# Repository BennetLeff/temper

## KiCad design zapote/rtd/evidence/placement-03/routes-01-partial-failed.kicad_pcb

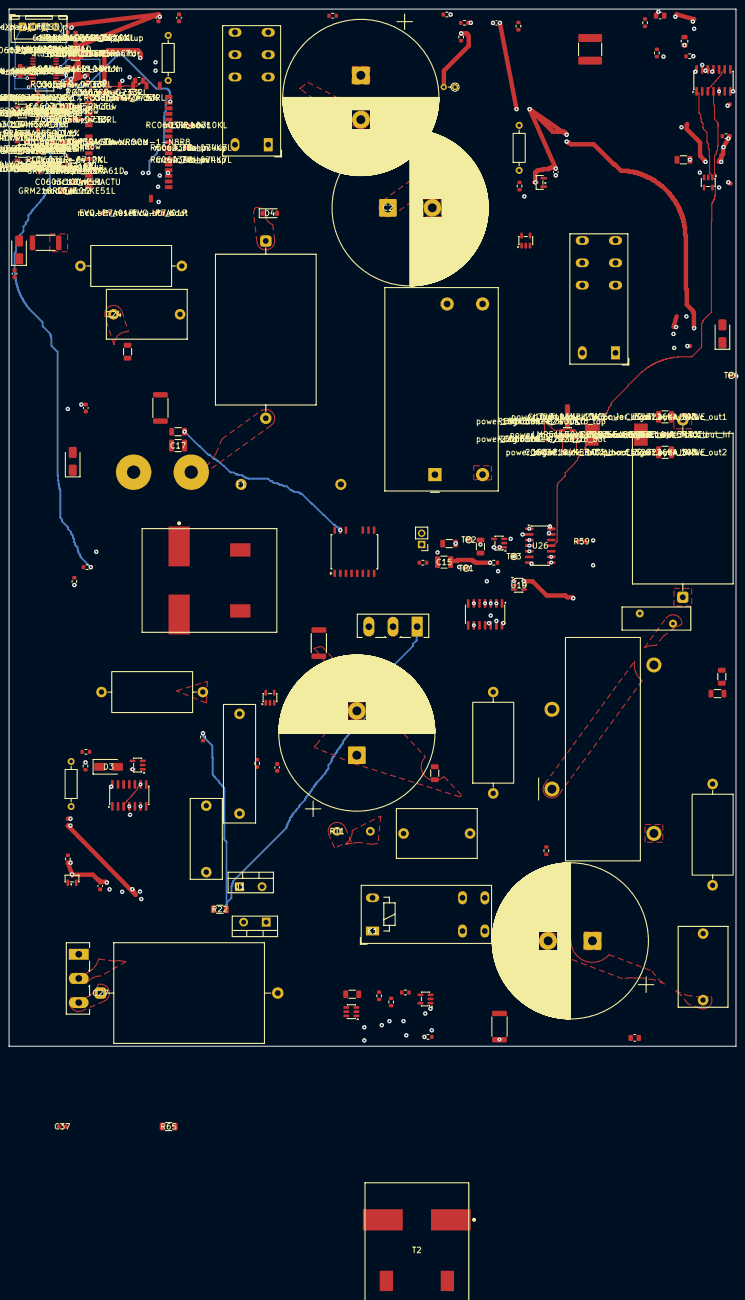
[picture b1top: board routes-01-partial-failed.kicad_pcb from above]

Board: 6 copper layers, 164.0 x 234.0 mm, 168 parts (0 on the bottom side), 110 nets.

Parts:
C1: ?; C_Rect_L18.0mm_W7.0mm_P15.00mm_FKS3_FKP3
C2, C3, C4, C5: ?; CP_Radial_D35.0mm_P10.00mm_SnapIn
C6: ?; C_Rect_L26.5mm_W7.0mm_P22.50mm_MKS4
C7, C8, C24: ?; C_Rect_L18.0mm_W11.0mm_P15.00mm_FKS3_FKP3
C9: CL32B106KBJZW6E; C_1210_3225Metric
C10, C13, C29, C30, C31, C32, C33, C34, C35, C39: C0603C104K5RACTU; C_0603_1608Metric
C11, C12: CL32B226KAJNNWE; C_1210_3225Metric
C14: ?; C_2220_5750Metric
C15, C17: ?; C_1210_3225Metric
C16, C18, C19, C20, C21, C22, C23, C28, C36, C37, C38: ?; C_0603_1608Metric
C25, C26, C27: ?; C_Axial_L34.0mm_D22.5mm_P40.00mm_Horizontal
C40: GRM21BR71A106KE51L; C_0805_2012Metric
C41: GRM188R71A105KA61D; C_0603_1608Metric
D1, D2, D3: ?; D_SMA
D4: ?; D_SOD-123
F1: ?; Fuse_Holder_5x20mm
J1: B4B-XH-A(LF)(SN); JST_XH_B4B-XH-A_1x04_P2.50mm_Vertical
J2: ?; PinHeader_1x02_P2.54mm_Vertical
K1: ?; Relay_SPST_Schrack-RT33K012
K2, K3: ?; Relay_SPDT_Schrack-RT314012
L1: ?; CMC_B82726S
L2: SRP1265A-5R6M; L_Bourns_SRP1265A
PS1: ?; Converter_ACDC_MeanWell_IRM-10-xx_THT
Q1, Q2: ?; SOT-23
R1, R60, R75: ?; R_Axial_DIN0207_L6.3mm_D2.5mm_P10.16mm_Horizontal
R2, R3, R12, R13: ?; R_0805_2012Metric
R4, R5, R14, R15: ?; R_2512_6332Metric
R6, R7, R8, R9: ?; R_Axial_DIN0918_L18.0mm_D9.0mm_P22.86mm_Horizontal
R10, R11, R18, R22, R25, R46, R47, R48, R51, R52, R53, R65: ?; R_1206_3216Metric
R16, R39: RC0603FR-07100KL; R_0603_1608Metric
R17: RC0603FR-0722K1L; R_0603_1608Metric
R19, R20, R21, R23, R24, R26, R27, R44, R45, R49, R50, R54, R56, R57, R58, R59, R61, R62, R63, R64, R66, R67, R68, R69, R70: ?; R_0603_1608Metric
R28: ERA-6AEB431V; R_0805_2012Metric
R29, R31, R32, R33: RC0603FR-0733RL; R_0603_1608Metric
R30: ?; LitzPad_15A
R34: BLM18AG121SN1D; L_0603_1608Metric
R35: ERA-3AEB6192V; R_0603_1608Metric
R36, R38: ERA-3AEB103V; R_0603_1608Metric
R37: ERA-3AEB5901V; R_0603_1608Metric
R40: ERA-6AEB6193V; R_0805_2012Metric
R41: ERA-3AEB104V; R_0603_1608Metric
R42, R43, R71, R72: RC0603FR-0710KL; R_0603_1608Metric
R55: ?; R_Axial_DIN0204_L3.6mm_D1.6mm_P2.54mm_Vertical
R73, R74: RC0603FR-074K7L; R_0603_1608Metric
RT1: ?; R_Disc_D15.0mm_W7.0mm_P7.5mm
RV1: ?; RV_Disc_D15.5mm_W5.2mm_P7.5mm
SW1, SW2: EVQ-P7A01P; R_0603_1608Metric
T1, T2: ?; CST3015
TP1, TP2, TP3, TP4: ?; TestPoint_Pad_D1.0mm
U1, U2: ?; TO-220-2_Vertical
U3: LMR51430XDDCR; SOT-23-6
U4, U5: ?; TO-247-3_Vertical
U6: ?; SOIC16W_Isolated
U7: ?; D_SMA
U8: MAX31865AAP+; SSOP-20_3.9x8.7mm_P0.635mm
U9: REF2025AIDDCR; SOT-23-5
U10, U11: TLV3201AIDBVR; SOT-23-5
U12: SN74LVC1G08DBVR; SOT-23-5
U13: TPS3700DDCR; SOT-23-6
U14: SN74LVC1G38DBVR; SOT-23-5
U15, U16, U17, U18, U19, U20, U22: ?; SOT-23-5
U21: ?; SOT-23-6
U23, U24, U25, U26: ?; SOIC-14_3.9x8.7mm_P1.27mm
U27: ESP32-S3-WROOM-1-N8R8; ESP32-S3-WROOM-1

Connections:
+3V3: C11.1, C12.1, C13.1, C20.1, C21.1, C30.1, C34.1, C38.1, C39.1, C40.1, L2.2, R16.1, R26.1, R34.1, R42.1, R43.1, R44.1, R56.1, R57.1, R61.1, R62.1, R66.1, R69.1, R70.1, R71.1, R72.1, R73.1, R74.1, U6.3, U6.8, U9.3, U9.4, U13.5, U15.5, U16.5, U17.5, U18.5, U19.5, U20.3, U20.5, U21.5, U22.2, U22.5, U23.14, U24.14, U25.14, U26.2, U26.13, U26.14, U27.2
+15V: C9.1, C15.1, C16.1, PS1.3, R1.1, R10.1, R11.1, R75.1, U3.3, U3.5
+15V_LS: C23.1, U6.11, U7.2
+170V_BUS: C2.1, C4.1, C14.1, C24.1, PS1.1, R4.1, R6.1, R46.1, R51.1, U1.1, U4.2
DC_BUS_RTN: C3.2, C5.2, C8.2, K3.1, R5.2, T2.2, U2.2
DISCHARGE_CTRL: R12.1, U27.24
GATE_HS: R18.1, U6.15
GATE_LS: R22.2, R23.1, U5.1
I_SENSE: C28.1, R25.1, R26.2, R27.1, T1.3, U15.3, U27.39
OCP2_VREF_2V5: U9.5, U16.4, U19.4
PWM_HS: R20.1, U27.4
PWM_LS: R21.1, U27.5
PWR_RTN: C2.2, C3.1, C4.2, C5.1, C6.1, C7.2, C14.2, K2.1, L1.3, PS1.2, R4.2, R5.1, R8.1, T1.2
RELAY_CTRL: R2.1, U27.9
RTD_CS_N: R32.1, U27.18
RTD_DRDY: U8.1, U27.17
RTD_HW_FAULT: R43.2, U14.4, U24.2
RTD_SCK: R29.1, U27.12
RTD_SDI: R31.1, U27.19
RTD_SDO: R33.2, U27.20
SHUTDOWN: TP1.1, TP2.1, U6.5, U26.6, U26.10, U27.10
SW_NODE: C25.1, C26.1, C27.1, D4.1, R19.2, U4.3, U5.2
V_BUS_SENSE: C36.1, R53.2, R54.1, U27.38
WDT_KICK: U20.4, U27.7
WDT_RESET_N: U20.2, U26.12, U27.6
ac_n: C1.2, L1.2, RV1.2
bias: R28.1, U8.4, U8.5
boot: C10.1, U3.6
cs_n: R32.2, U8.16
discharge.k_dis1-coil1: D2.1, K2.2, R10.2
discharge.k_dis1-coil2: D2.2, D3.2, K2.5, K3.5, Q2.1
discharge.k_dis1-nc: K2.4, R7.2, R14.1
discharge.k_dis2-coil1: D3.1, K3.2, R11.2
discharge.k_dis2-nc: K3.4, R9.2, R15.1
discharge.q_dis_drv-g: Q2.2, R12.2, R13.1
discharge.r_dis1a-p2: R6.2, R7.1
discharge.r_dis2a-p2: R8.2, R9.1
discharge.r_snub1-p2: C7.1, R14.2
discharge.r_snub2-p2: C8.1, R15.2
en: C41.1, R71.2, SW1.1, U27.3
fb: R16.2, R17.1, U3.4
gnd: C6.2, C9.2, C11.2, C12.2, C13.2, C15.2, C16.2, C18.2, C19.2, C20.2, C21.2, C28.2, C29.2, C30.2, C31.2, C32.2, C33.2, C34.2, C35.2, C36.2, C37.2, C38.2, C39.2, C40.2, C41.2, J2.2, PS1.4, Q1.3, Q2.3, R3.2, R13.2, R17.2, R24.2, R25.2, R27.2, R36.2, R38.2, R39.2, R41.2, R45.2, R49.2, R54.2, R55.2, R58.2, R60.2, R63.2, R65.2, R67.2, SW1.2, SW2.2, T1.4, T2.4, U3.1, U6.4, U8.9, U8.13, U8.18, U8.19, U9.2, U10.2, U11.2, U12.3, U13.2, U13.4, U14.3, U15.2, U16.2, U17.2, U18.2, U19.2, U20.1, U21.2, U21.4, U22.3, U23.7, U23.11, U23.12, U23.13, U24.5, U24.7, U24.11, U24.12, U24.13, U25.5, U25.7, U25.8, U25.11, U25.12, U25.13, U26.7, U27.1
hb-gnd: C23.2, C24.2, R23.2, T2.1, U5.3, U6.9
hb.gate_hs.driver-p1: R24.1, U6.6
hb.gate_hs.driver-p1-1: C17.1, C22.1, U6.16, U7.1
hb.gate_hs.driver-p2: C17.2, C22.2, D4.2, U6.14
hb.power_loop.q_high-g: R18.2, R19.1, U4.1
i2c_scl_ui: R74.2, U27.32
i2c_sda_ui: R73.2, U27.31
ina: C18.1, R20.2, U6.1
inb: C19.1, R21.2, U6.2
input: R22.1, U6.10
io0: R72.2, SW2.1, U27.27
power_in.bypass_relay-coil1: D1.1, K1.1, R1.2
power_in.bypass_relay-coil2: D1.2, K1.2, Q1.1
power_in.ntc-no: K1.3, RT1.2, U1.2, U2.1
power_in.q_relay_drv-g: Q1.2, R2.2, R3.1
refin_n: R28.2, U8.6, U8.7, U10.3, U11.4
rtd_force_n: J1.4, U8.12
rtd_force_p: J1.1, U8.8
rtd_pan.high_window-out: U11.1, U12.2
rtd_pan.low_window-out: U10.1, U12.1
rtd_pan.r_high_top-inp: R37.2, R38.1, U11.3
rtd_pan.r_low_top-inn: R35.2, R36.1, U10.4
rtd_pan.rail_monitor-ina_p: R40.2, R41.1, U13.3
rtd_pan.rail_monitor-outa: R42.2, U13.1, U14.2
rtd_sense_n: J1.3, U8.11
rtd_sense_p: J1.2, U8.10
s1: C37.1, R65.1, T2.3, U19.3
safety-line: R55.1, R56.2, U17.4, U27.15
safety-line-1: R60.1, R61.2, U18.4
safety-line-2: U24.4, U27.22
safety-line-3: U23.5, U27.8
safety.coil_thermal-line: R64.2, U18.1, U24.8
safety.coil_thermal.comp-inp: R62.2, R63.1, R64.1, U18.3
safety.fault_any_or-a2: U24.3, U24.9, U25.3
safety.fault_any_or-y2: U24.6, U26.9
safety.fault_or3-b2: U25.4, U25.9
safety.fault_or3-y2: U25.6, U26.1
safety.fault_or-a2: U23.3, U23.9
safety.fault_or-b2: U23.4, U26.11
safety.fault_or-y2: U23.6, U24.1
safety.latch-b2: U26.5, U26.8
safety.ocp2-line: TP3.1, U19.1, U25.2
safety.ocp-line: U15.1, U23.1
safety.ocp.comp-inn: R44.2, R45.1, U15.4
safety.ovp-line: R50.2, U16.1, U23.2
safety.ovp.comp-inp: R48.2, R49.1, R50.1, U16.3
safety.ovp.r_adc_top1-p2: R51.2, R52.1
safety.ovp.r_adc_top2-p2: R52.2, R53.1
safety.ovp.r_div_top1-p2: R46.2, R47.1
safety.ovp.r_div_top2-p2: R47.2, R48.1
safety.thermal-line: R59.2, U17.1, U23.8
safety.thermal.comp-inp: R57.2, R58.1, R59.1, U17.3
safety.uvlo_logic-line: R70.2, TP4.1, U22.4, U25.1
safety.uvlo_logic.mon-ina_p: R66.2, R67.1, R68.1, U21.3
safety.uvlo_logic.mon-outa: R68.2, R69.2, U21.1, U22.1
sclk: R29.2, U8.15
sdi: R31.2, U8.14
sdo: R33.1, U8.17
sw: C10.2, L2.1, U3.2
tank-out: R30.2, T1.1
tank.c_tank1-p2: C25.2, C26.2, C27.2, R30.1
thermal.j_fan-p1: J2.1, R75.2
vbias: R35.1, R37.1, U9.1
vcc: C29.1, C31.1, C32.1, C33.1, C35.1, R34.2, R40.1, U8.2, U8.3, U10.5, U11.5, U12.5, U14.5
w1_1: C1.1, F1.2, L1.1, RV1.1
w1_2: K1.4, L1.4, RT1.1
y: R39.1, U12.4, U14.1
y1: U26.3, U26.4

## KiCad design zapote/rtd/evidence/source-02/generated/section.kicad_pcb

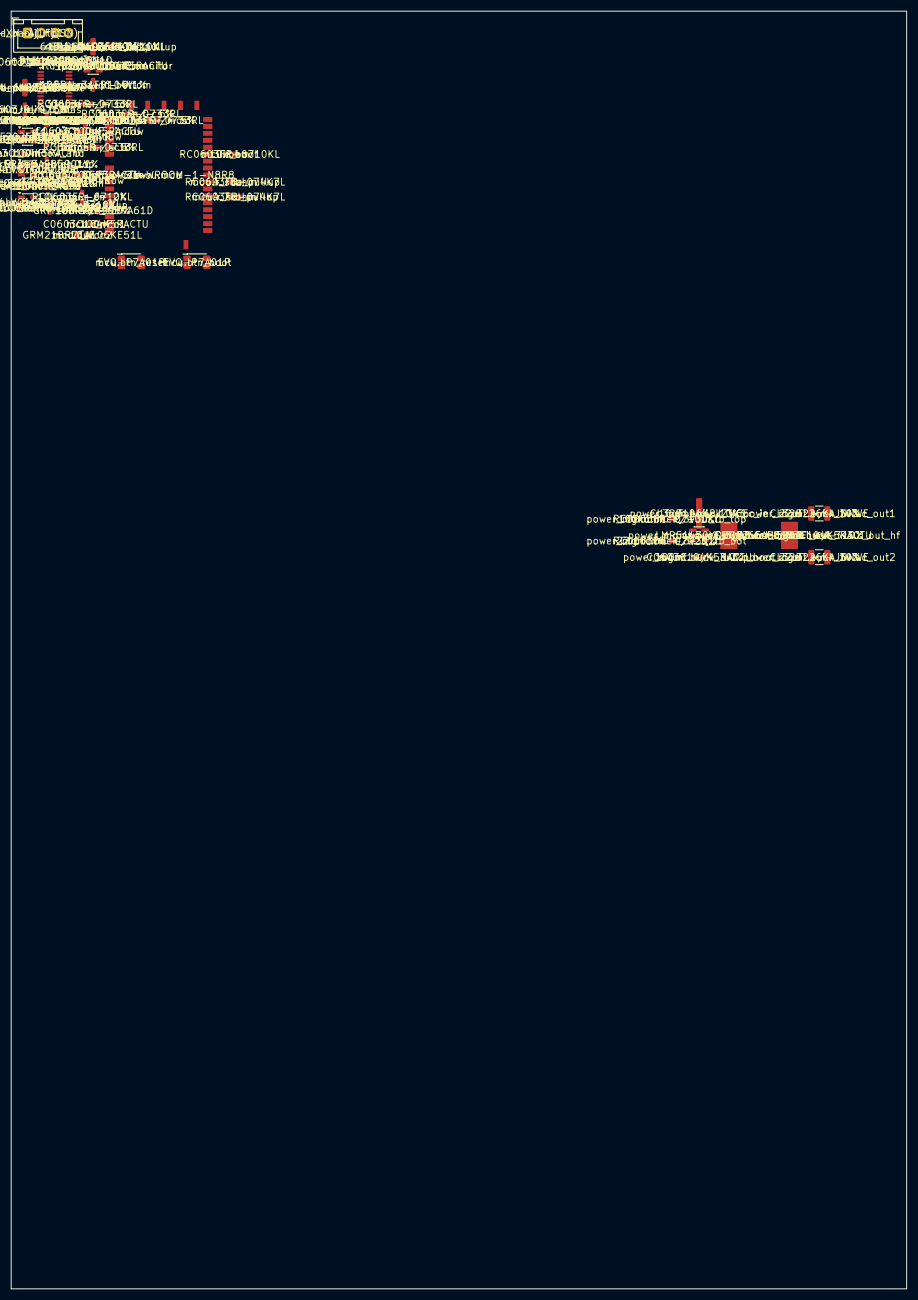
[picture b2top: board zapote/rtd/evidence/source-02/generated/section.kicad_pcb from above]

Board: 6 copper layers, 164.0 x 234.0 mm, 52 parts (0 on the bottom side), 35 nets, no tracks yet.

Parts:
C9: CL32B106KBJZW6E; C_1210_3225Metric
C10, C13, C29, C31, C32, C33, C34, C35, C36, C40: C0603C104K5RACTU; C_0603_1608Metric
C11, C12: CL32B226KAJNNWE; C_1210_3225Metric
C30: C0603C102J5GACTU; C_0603_1608Metric
C41: GRM21BR71A106KE51L; C_0805_2012Metric
C42: GRM188R71A105KA61D; C_0603_1608Metric
J1: B4B-XH-A(LF)(SN); JST_XH_B4B-XH-A_1x04_P2.50mm_Vertical
L2: SRP1265A-5R6M; L_Bourns_SRP1265A
R16, R41: RC0603FR-07100KL; R_0603_1608Metric
R17: RC0603FR-0722K1L; R_0603_1608Metric
R28: ERA-6AEB431V; R_0805_2012Metric
R29, R31: RC0603JR-071ML; R_0603_1608Metric
R32, R33, R34, R35: RC0603FR-0733RL; R_0603_1608Metric
R36: BLM18AG121SN1D; L_0603_1608Metric
R37: ERA-3AEB6192V; R_0603_1608Metric
R38, R40: ERA-3AEB103V; R_0603_1608Metric
R39: ERA-3AEB5901V; R_0603_1608Metric
R42: ERA-6AEB6193V; R_0805_2012Metric
R43: ERA-3AEB104V; R_0603_1608Metric
R44, R45, R73, R74: RC0603FR-0710KL; R_0603_1608Metric
R75, R76: RC0603FR-074K7L; R_0603_1608Metric
SW1, SW2: EVQ-P7A01P; SW_SPST_EVQP7A
U3: LMR51430XDDCR; SOT-23-6
U8: MAX31865AAP+; SSOP-20_3.9x8.7mm_P0.635mm
U9: REF2025AIDDCR; SOT-23-5
U10, U11: TLV3201AIDBVR; SOT-23-5
U12: SN74LVC1G08DBVR; SOT-23-5
U13: TPS3700DDCR; SOT-23-6
U14: SN74LVC1G38DBVR; SOT-23-5
U27: ESP32-S3-WROOM-1-N8R8; ESP32-S3-WROOM-1

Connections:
+3V3: C11.1, C12.1, C13.1, C31.1, C35.1, C40.1, C41.1, L2.2, R16.1, R36.1, R44.1, R45.1, R73.1, R74.1, R75.1, R76.1, U9.3, U9.4, U13.5, U27.2
+15V: C9.1, U3.3, U3.5
RTD_CS_N: R34.1, U27.18
RTD_DRDY: U8.1, U27.17
RTD_HW_FAULT: R45.2, U14.4
RTD_SCK: R32.1, U27.12
RTD_SDI: R33.1, U27.19
RTD_SDO: R35.2, U27.20
bias: R28.1, R29.2, R31.2, U8.4, U8.5
boot: C10.1, U3.6
cs_n: R34.2, U8.16
en: C42.1, R73.2, SW1.1, U27.3
fb: R16.2, R17.1, U3.4
gnd: C9.2, C11.2, C12.2, C13.2, C29.2, C31.2, C32.2, C33.2, C34.2, C35.2, C36.2, C40.2, C41.2, C42.2, R17.2, R38.2, R40.2, R41.2, R43.2, SW1.2, SW2.2, U3.1, U8.9, U8.13, U8.18, U8.19, U9.2, U10.2, U11.2, U12.3, U13.2, U13.4, U14.3, U27.1
i2c_scl_ui: R76.2, U27.32
i2c_sda_ui: R75.2, U27.31
io0: R74.2, SW2.1, U27.27
refin_n: R28.2, U8.6, U8.7, U10.3, U11.4
rtd_force_n: J1.4, U8.12
rtd_force_p: J1.1, U8.8
rtd_pan.high_window-out: U11.1, U12.2
rtd_pan.low_window-out: U10.1, U12.1
rtd_pan.r_high_top-inp: R39.2, R40.1, U11.3
rtd_pan.r_low_top-inn: R37.2, R38.1, U10.4
rtd_pan.rail_monitor-ina_p: R42.2, R43.1, U13.3
rtd_pan.rail_monitor-outa: R44.2, U13.1, U14.2
rtd_sense_n: C30.2, J1.3, R31.1, U8.11
rtd_sense_p: C30.1, J1.2, R29.1, U8.10
sclk: R32.2, U8.15
sdi: R33.2, U8.14
sdo: R35.1, U8.17
sw: C10.2, L2.1, U3.2
vbias: R37.1, R39.1, U9.1
vcc: C29.1, C32.1, C33.1, C34.1, C36.1, R36.2, R42.1, U8.2, U8.3, U10.5, U11.5, U12.5, U14.5
y: R41.1, U12.4, U14.1

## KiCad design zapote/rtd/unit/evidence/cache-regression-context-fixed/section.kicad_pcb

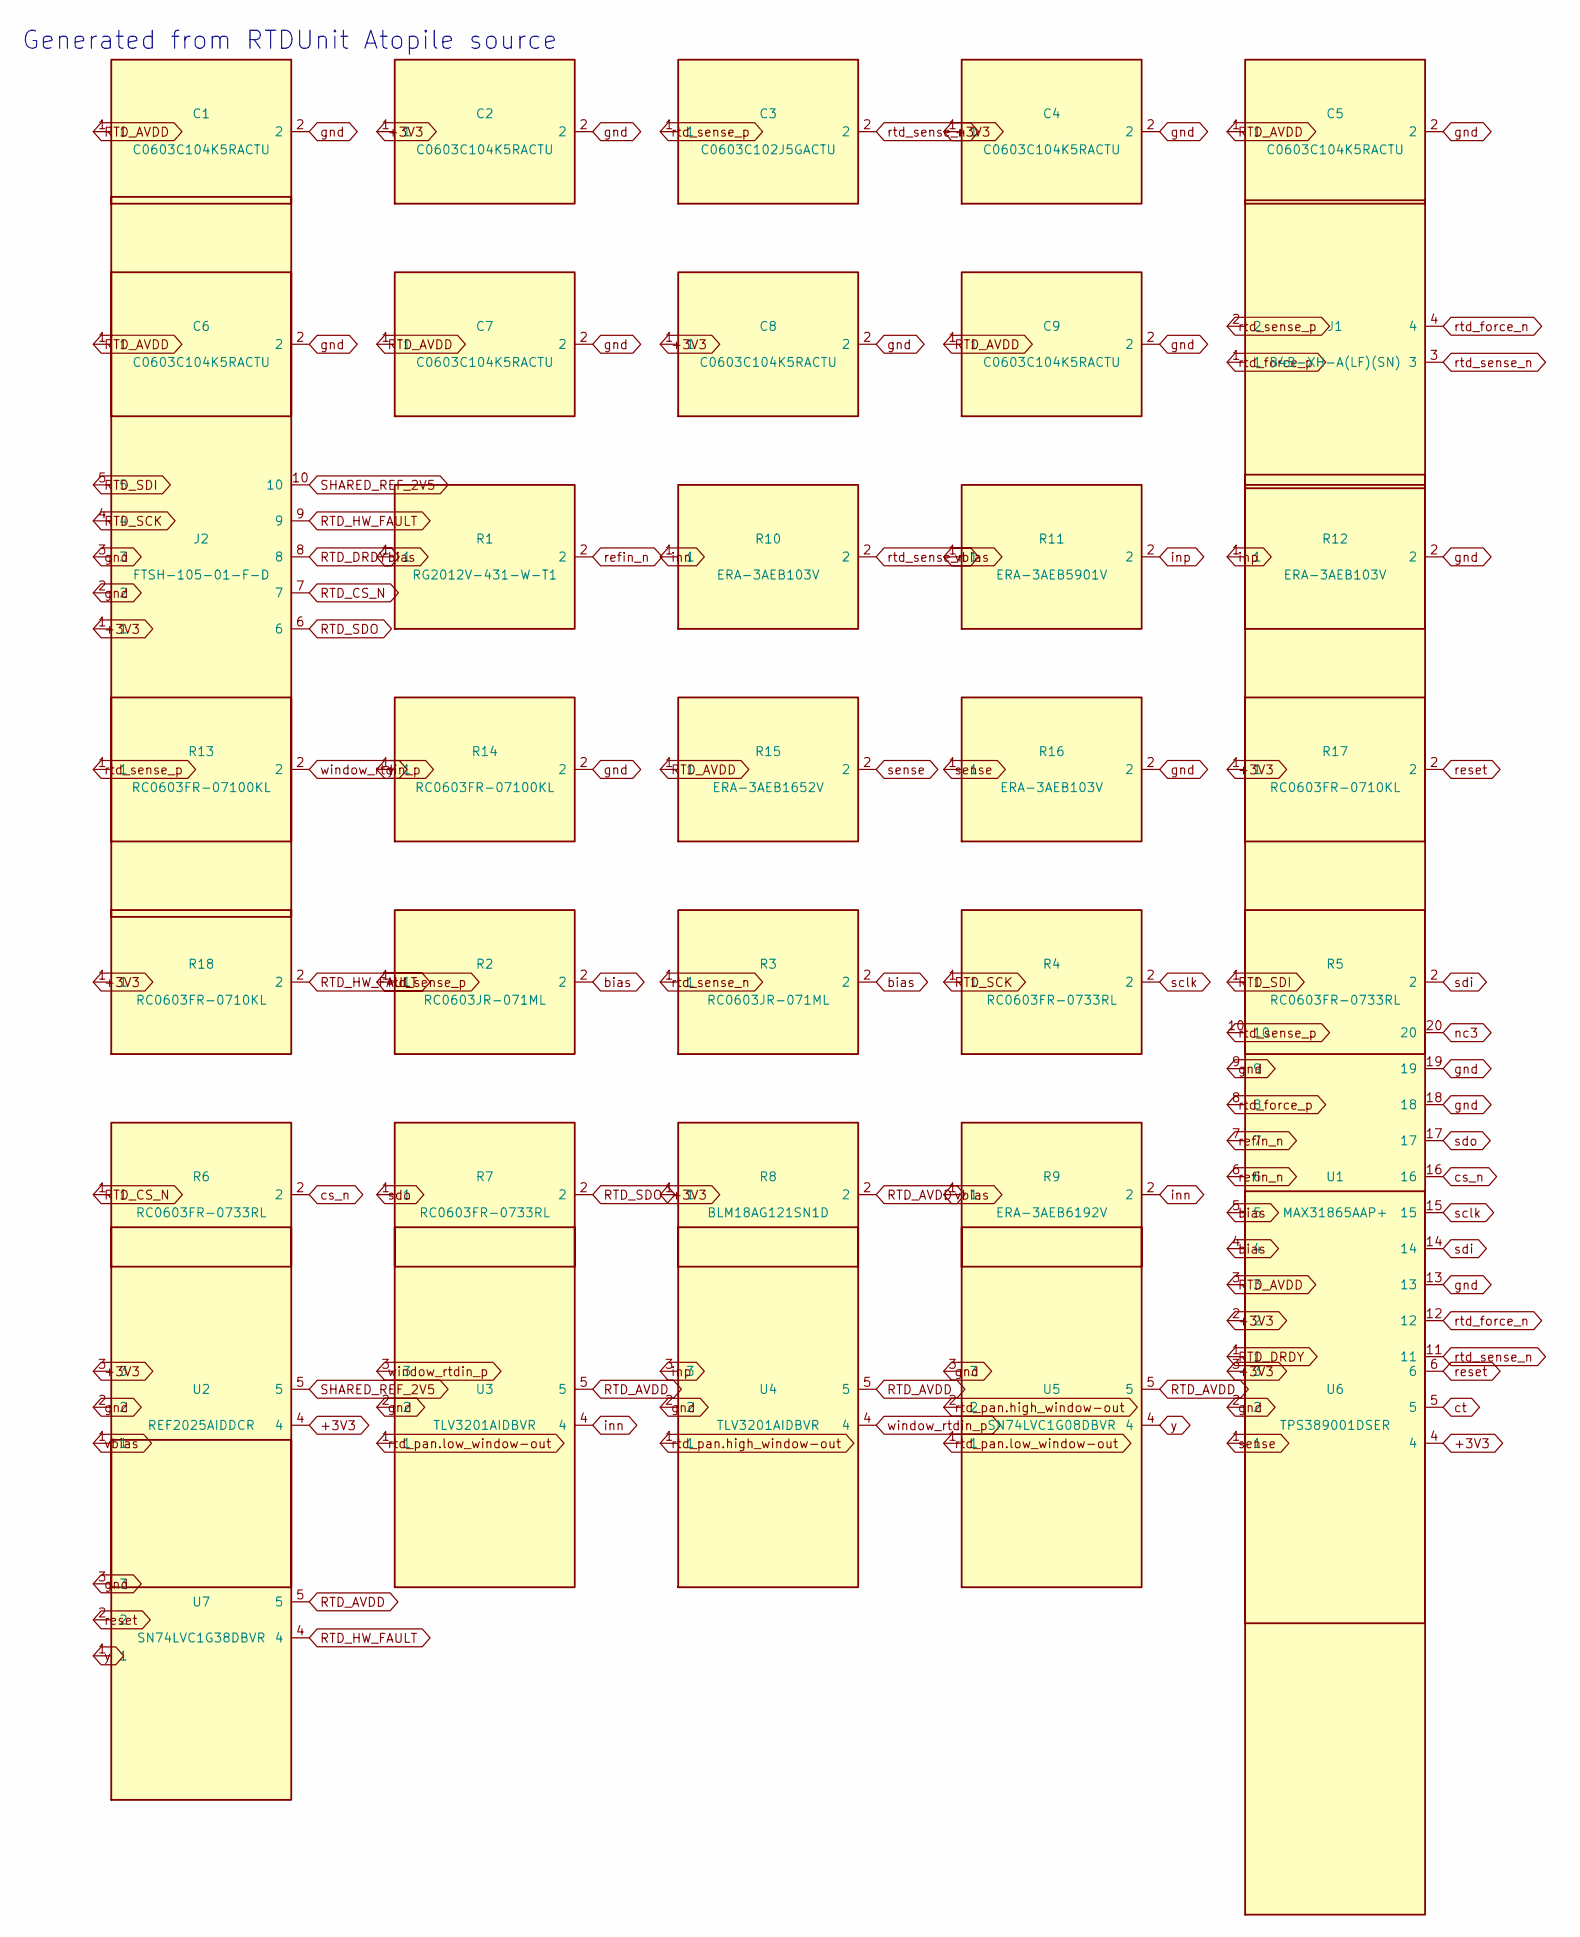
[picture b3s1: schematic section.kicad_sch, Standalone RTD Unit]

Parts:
C1, C2, C4, C5, C6, C7, C8, C9: C0603C104K5RACTU; C_0603_1608Metric
C3: C0603C102J5GACTU; C_0603_1608Metric
J1: B4B-XH-A(LF)(SN); JST_XH_B4B-XH-A_1x04_P2.50mm_Vertical
J2: FTSH-105-01-F-D; FTSH-105-01-F-D_2x5_P1.27mm
R1: RG2012V-431-W-T1; R_0805_2012Metric
R2, R3: RC0603JR-071ML; R_0603_1608Metric
R4, R5, R6, R7: RC0603FR-0733RL; R_0603_1608Metric
R8: BLM18AG121SN1D; L_0603_1608Metric
R9: ERA-3AEB6192V; R_0603_1608Metric
R10, R12, R16: ERA-3AEB103V; R_0603_1608Metric
R11: ERA-3AEB5901V; R_0603_1608Metric
R13, R14: RC0603FR-07100KL; R_0603_1608Metric
R15: ERA-3AEB1652V; R_0603_1608Metric
R17, R18: RC0603FR-0710KL; R_0603_1608Metric
U1: MAX31865AAP+; SSOP-20_3.9x8.7mm_P0.635mm
U2: REF2025AIDDCR; SOT-23-5
U3, U4: TLV3201AIDBVR; SOT-23-5
U5: SN74LVC1G08DBVR; SOT-23-5
U6: TPS389001DSER; TPS389001DSER_WSON-6_DSE
U7: SN74LVC1G38DBVR; SOT-23-5

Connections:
+3V3: C2.1, C4.1, C8.1, J2.1, R8.1, R17.1, R18.1, U1.2, U2.3, U2.4, U6.3, U6.4
RTD_AVDD: C1.1, C5.1, C6.1, C7.1, C9.1, R8.2, R15.1, U1.3, U3.5, U4.5, U5.5, U7.5
RTD_CS_N: J2.7, R6.1
RTD_DRDY: J2.8, U1.1
RTD_HW_FAULT: J2.9, R18.2, U7.4
RTD_SCK: J2.4, R4.1
RTD_SDI: J2.5, R5.1
RTD_SDO: J2.6, R7.2
SHARED_REF_2V5: J2.10, U2.5
bias: R1.1, R2.2, R3.2, U1.4, U1.5
cs_n: R6.2, U1.16
ct: U6.5
gnd: C1.2, C2.2, C4.2, C5.2, C6.2, C7.2, C8.2, C9.2, J2.2, J2.3, R12.2, R14.2, R16.2, U1.9, U1.13, U1.18, U1.19, U2.2, U3.2, U4.2, U5.3, U6.2, U7.3
inn: R9.2, R10.1, U3.4
inp: R11.2, R12.1, U4.3
nc3: U1.20
refin_n: R1.2, U1.6, U1.7
reset: R17.2, U6.6, U7.2
rtd_force_n: J1.4, U1.12
rtd_force_p: J1.1, U1.8
rtd_pan.high_window-out: U4.1, U5.2
rtd_pan.low_window-out: U3.1, U5.1
rtd_sense_n: C3.2, J1.3, R3.1, R10.2, U1.11
rtd_sense_p: C3.1, J1.2, R2.1, R13.1, U1.10
sclk: R4.2, U1.15
sdi: R5.2, U1.14
sdo: R7.1, U1.17
sense: R15.2, R16.1, U6.1
vbias: R9.1, R11.1, U2.1
window_rtdin_p: R13.2, U3.3, U4.4
y: R14.1, U5.4, U7.1

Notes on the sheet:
Generated from RTDUnit Atopile source

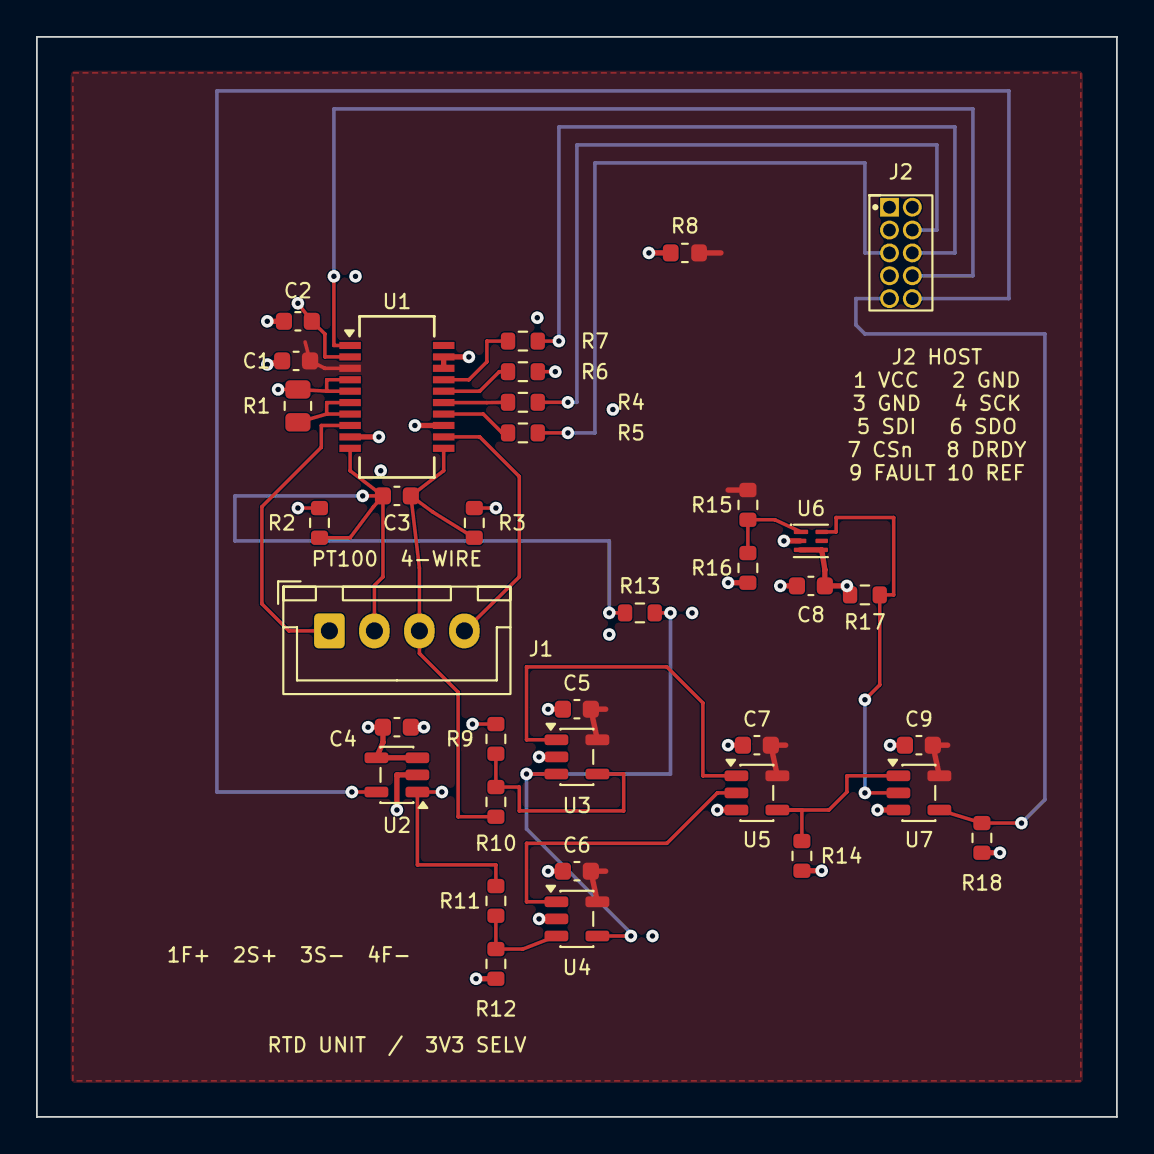
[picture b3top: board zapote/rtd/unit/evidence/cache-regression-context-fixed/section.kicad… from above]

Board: 4 copper layers, 60.0 x 60.0 mm, 36 parts (0 on the bottom side), 29 nets.
